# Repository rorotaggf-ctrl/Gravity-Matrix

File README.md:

# Gravity-Matrix

An interactive physics simulation, digital sand toy, and graphical desk instrument powered by an ESP32, developed for **Hack Club Half-Life (Week 4: Displays)**.  
The system captures board tilt and physical impacts via a 6-axis MPU-6050 IMU and drives a 1.3" IPS TFT display (240x240, ST7789 controller via SPI). The firmware features an interactive tilt menu, a real-time cellular automata sand simulation with dynamic avalanche collision handling, and a trigonometric analog clock GUI with flicker-free differential rendering.

---

## Features

- **Microcontroller:** ESP32 NodeMCU (Xtensa dual-core LX6, 240 MHz, 320 KB SRAM, USB-C).
- **Display Module:** 1.3" IPS full-color screen (240x240 pixels, 65K colors, ST7789 controller via hardware SPI).
- **Inertial Sensor:** GY-521 Breakout (MPU-6050 3-axis accelerometer + 3-axis gyroscope via Fast-Mode I2C at 400 kHz).
- **Cellular Automata Sand Engine:** Real-time 60x60 particle simulation ($4 \times 4$ pixel grain scaling) calculating gravity slip, granular resting angles, and shake agitation.
- **Trigonometric Analog Clock GUI:** Real-time geometric watchface with trigonometric ($sin / cos$) hand vectoring and differential rendering (erasing and drawing only modified vectors to eliminate display flicker).
- **Tilt-Controlled Menu System:** Gesture-driven UI allowing mode selection via pitch/roll tilt and shake gestures without physical buttons.
- **Power Delivery:** Powered directly via the USB-C port with ceramic decoupling capacitors (100nF) on peripheral rails.
- **Modular Sockets:** All major components mount into 2.54mm female pin headers for serviceability.

---

## Pinout Configuration

| Component | Pin Label | ESP32 Pin / GPIO | Protocol / Function | Description |
| :--- | :--- | :--- | :--- | :--- |
| **ST7789 Display** | GND | GND | Power | Ground connection |
| **ST7789 Display** | VCC | 3V3 | Power | 3.3V Logic & Driver Power |
| **ST7789 Display** | SCL | GPIO 18 | VSPI SCK | Hardware SPI Clock |
| **ST7789 Display** | SDA | GPIO 23 | VSPI MOSI | Hardware SPI Master Out |
| **ST7789 Display** | RES | GPIO 4 | GPIO Output | Hardware Reset Line |
| **ST7789 Display** | DC | GPIO 2 | GPIO Output | Data / Command Selection |
| **ST7789 Display** | BLK | 3V3 | Power | Backlight Constant Enable |
| **MPU-6050 Sensor** | VCC | 3V3 | Power | Sensor Core Power |
| **MPU-6050 Sensor** | GND | GND | Power | Ground connection |
| **MPU-6050 Sensor** | SCL | GPIO 22 | I2C SCL | Fast-Mode I2C Clock (400 kHz) |
| **MPU-6050 Sensor** | SDA | GPIO 21 | I2C SDA | Fast-Mode I2C Data |

---

## Bill of Materials (Grant Funded)

> [!NOTE]
> This parts list covers items funded via Hack Club Half-Life ($30.00 Tier 1 Limit).

| Part | What it's for | Qty | Price (USD) | Price (EUR) | Vendor | Purchase Link |
| :--- | :--- | :--- | :--- | :--- | :--- | :--- |
| Fasizi 1.3" IPS TFT Display (ST7789) | Primary visual display for cellular automata | 1 | $7.83 | 6,99 € | Amazon | [Amazon Link](https://www.amazon.de/dp/B09Z299F3Q) |
| ICQUANZX GY-521 MPU6050 Sensor | 6-axis tilt and acceleration tracking | 1 | $6.71 | 5,99 € | Amazon | [Amazon Link](https://www.amazon.de/dp/B07P963VNL) |
| ESP32 NodeMCU WROOM-32E Dev Board | Main computational processor | 1 | $5.03 | 4,49 € | eBay | [eBay Link](https://www.ebay.de/itm/157477097103) |
| Domestic Shipping (Germany) | Tracked delivery for ESP32 | 1 | $3.35 | 2,99 € | eBay | [eBay Link](https://www.ebay.de/itm/157477097103) |
| Gtziqa 100nF Ceramic Capacitors (150-Pack) | Power supply decoupling & noise filtering | 1 | $6.26 | 5,59 € | Amazon | [Amazon Link](https://www.amazon.de/dp/B0CX1TV9G7) |
| **Total Grant Cost** | | | **$29.18** | **26,05 €** | | |

*Remaining Tier 1 Budget: $0.82*

---

## Additional Self-Funded Components

> [!IMPORTANT]
> The following items are self-funded or sourced from existing workshop inventory to keep the project strictly within the grant limits.

| Part | What it's for | Qty | Price (USD) | Price (EUR) | Vendor | Purchase Link |
| :--- | :--- | :--- | :--- | :--- | :--- | :--- |
| Custom 2-Layer PCB (5 copies) | Mainboard carrier PCB | 1 | $8.10 | 7,23 € | JLCPCB | [JLCPCB Quote](https://jlcpcb.com/quote) |
| PCB Shipping (Standard Line) | Delivery to Germany | 1 | $9.55 | 8,53 € | JLCPCB | [JLCPCB Quote](https://jlcpcb.com/quote) |
| Female Pin Headers 2.54mm | Sockets for ESP32 and modules | 1 | $0.00 | 0,00 € | Inventory | Existing parts |
| M3 Standoffs & Screws | Mechanical mounting hardware | 4 | $0.00 | 0,00 € | Inventory | Existing parts |
| **Total Self-Funded** | | | **$17.65** | **15,76 €** | | |

---

## Hardware Design & Schematics

### KiCad Schematic View
Complete circuit diagram connecting the ESP32 NodeMCU socket headers to the SPI display bus, fast-mode I2C accelerometer, and rail decoupling capacitors.

### KiCad PCB Layout & Trace Routing
Two-layer carrier board layout with routed differential SPI/I2C signals, optimized component placement, and ground plane fills on both layers.

---

## Firmware Architecture & Implementation

Development is carried out in **VS Code** using **PlatformIO** and the Espressif 32 framework, organized in a modular structure:

- **`config.h`:** Global pin definitions for hardware SPI (GPIO 18, 23, 2, 4) and I2C buses (GPIO 21, 22), screen dimensions, and RGB565 color definitions.
- **`imu.h` / `imu.cpp`:** Direct-register I2C driver for MPU-6050 streaming raw 3-axis acceleration and tilt data without high overhead.
- **`sand_view.h` / `sand_view.cpp`:** Real-time falling sand simulation executing on a 60x60 grid with selective pixel differential drawing for flicker-free 30+ FPS refresh rates.
- **`clock_view.h` / `clock_view.cpp`:** Analog watchface GUI calculating hand positions trigonometrically ($sin / cos$) with selective line redraws to prevent full-screen redraw artifacts.
- **`menu_view.h` / `menu_view.cpp`:** Tilt-driven selection state machine navigating between instruments via real-time roll/pitch thresholds.
- **`main.cpp`:** Central execution loop orchestrating sensor updates and instrument transitions.

### Development Status
- [x] Universal automated Git sync scripts (`sync.sh` / `sync.ps1`).
- [x] MPU-6050 direct raw register polling over I2C bus (Registers `0x3B`–`0x40`).
- [x] Modular hardware configuration and display initialization via SPI.
- [x] Real-time cellular automata particle engine with avalanche sliding.
- [x] Trigonometric analog clock GUI with flicker-free differential line updates.
- [x] Tilt and shake gesture navigation state machine.
- [ ] Final integration run on physical carrier board.

### Firmware Source Snapshots

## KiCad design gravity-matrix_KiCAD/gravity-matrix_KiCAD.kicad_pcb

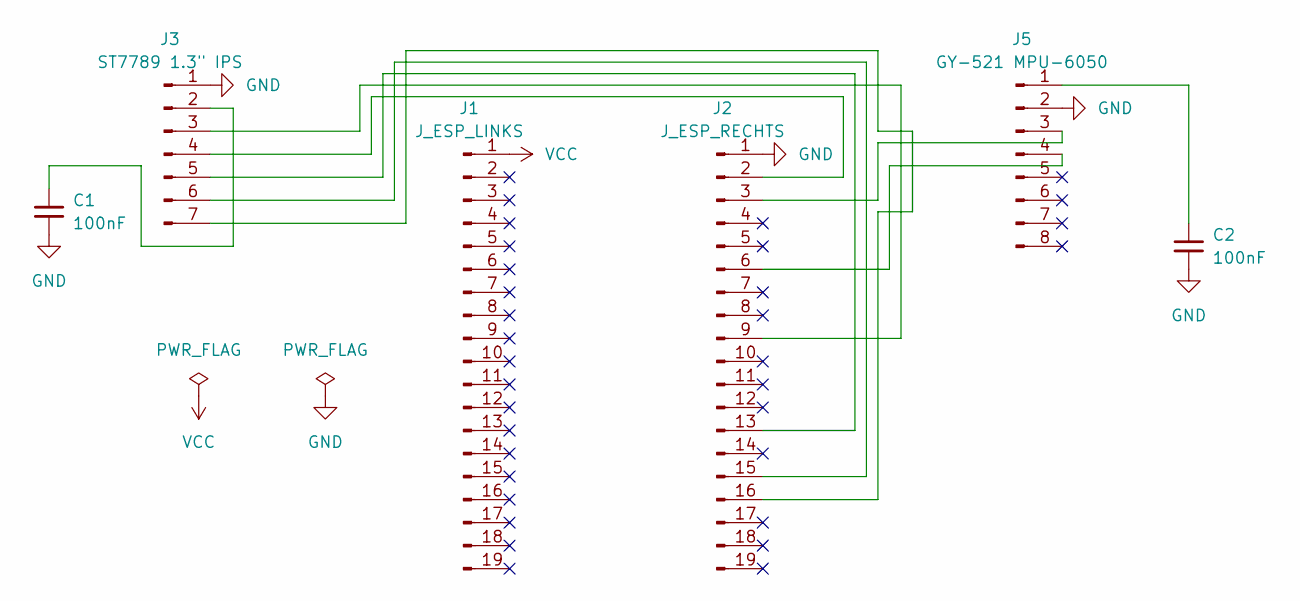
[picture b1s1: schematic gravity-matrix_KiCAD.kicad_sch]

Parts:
C1, C2: 100nF; C_Disc_D5.0mm_W2.5mm_P5.00mm
J1: J_ESP_LINKS; PinSocket_1x19_P2.54mm_Vertical
J2: J_ESP_RECHTS; PinSocket_1x19_P2.54mm_Vertical
J3: ST7789 1.3" IPS; PinSocket_1x07_P2.54mm_Vertical
J5: GY-521 MPU-6050; PinSocket_1x08_P2.54mm_Vertical

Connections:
GND: C1.2, C2.2, J2.1, J3.1, J5.2
unnamed: J2.2, J3.4
unnamed: J2.3, J5.3
unnamed: J2.6, J5.4
unnamed: J2.9, J3.3
unnamed: J2.13, J3.5
unnamed: J2.15, J3.6
unnamed: J2.16, J3.7
unnamed: C1.1, J3.2
unnamed: C2.1, J5.1
VCC: J1.1 (Pin_1_1)

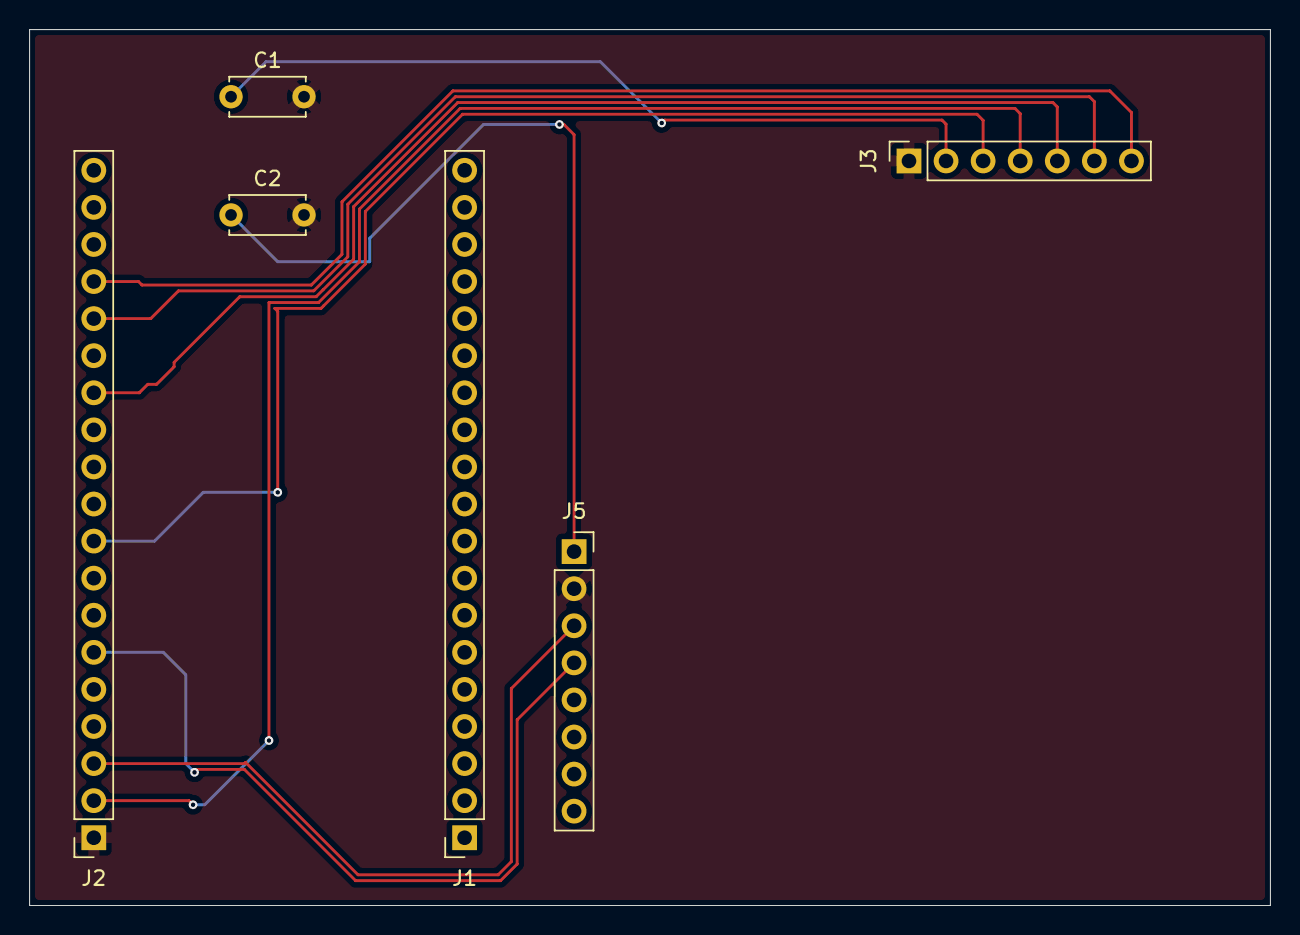
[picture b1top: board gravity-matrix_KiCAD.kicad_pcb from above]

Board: 2 copper layers, 85.0 x 60.0 mm, 6 parts (0 on the bottom side), 10 nets.
